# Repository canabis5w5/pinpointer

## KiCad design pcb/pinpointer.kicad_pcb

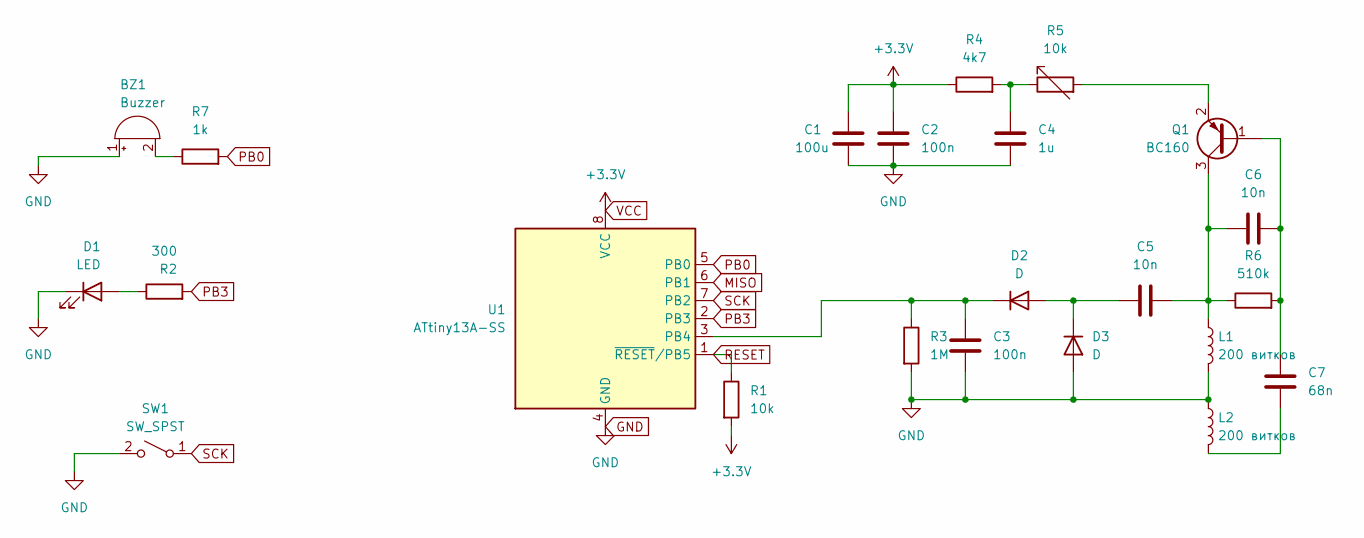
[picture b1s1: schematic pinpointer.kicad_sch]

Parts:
BZ1: Buzzer; R_Axial_DIN0207_L6.3mm_D2.5mm_P7.62mm_Horizontal
C1: 100u; C_1206_3216Metric
C2, C3: 100n; C_1206_3216Metric
C4: 1u; CP_EIA-3216-10_Kemet-I
C5, C6: 10n; C_1206_3216Metric
C7: 68n; C_1206_3216Metric
D1: LED; D_1206_3216Metric
D2, D3: D; D_1206_3216Metric
L1, L2: 200 витков; C_Radial_D6.3mm_H11.0mm_P2.50mm
Q1: BC160; SOT-23
R1, R5: 10k; R_1206_3216Metric
R2: 300; R_1206_3216Metric
R3: 1M; R_1206_3216Metric
R4: 4k7; R_1206_3216Metric
R6: 510k; R_1206_3216Metric
R7: 1k; R_1206_3216Metric
SW1: SW_SPST; SW_PUSH_6mm
U1: ATtiny13A-SS; SOIC-8_3.9x4.9mm_P1.27mm

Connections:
GND: BZ1.1 (-), C1.2, C2.2, C3.2, C4.2, D1.1 (K), D3.2 (A), L1.2, L2.1, R3.2, SW1.2 (B), U1.4 (GND)
MISO: U1.6 (PB1)
unnamed: BZ1.2 (+), R7.1
unnamed: C4.1, R4.2, R5.1
unnamed: C7.2, L2.2
unnamed: D1.2 (A), R2.1
unnamed: C5.1, D2.2 (A), D3.1 (K)
unnamed: C3.1, D2.1 (K), R3.1, U1.3 (PB4)
unnamed: C6.2, C7.1, Q1.1 (B), R6.2
unnamed: C5.2, C6.1, L1.1, Q1.3 (C), R6.1
unnamed: Q1.2 (E), R5.2
PB0: R7.2, U1.5 (PB0)
PB3: R2.2, U1.2 (PB3)
RESET: R1.1, U1.1 (~RESET/PB5)
SCK: SW1.1 (A), U1.7 (PB2)
VCC: C1.1, C2.1, R1.2, R4.1, U1.8 (VCC)

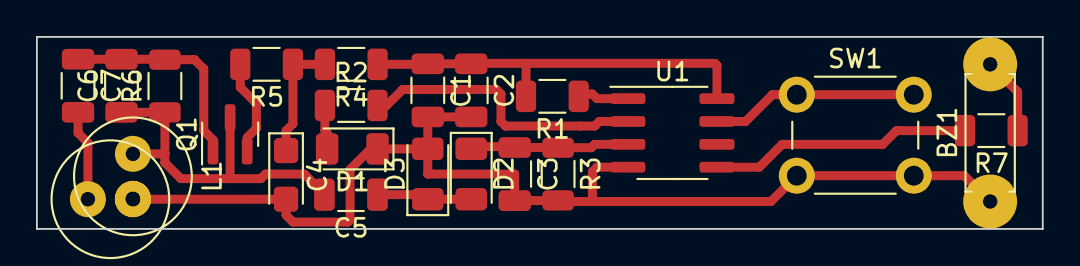
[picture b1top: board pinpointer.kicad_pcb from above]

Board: 2 copper layers, 55.9 x 10.7 mm, 23 parts (0 on the bottom side), 15 nets.

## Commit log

2023-10-08 pcb
    circuit diagram
2023-10-19 any changes
2023-10-20 fix bugs
